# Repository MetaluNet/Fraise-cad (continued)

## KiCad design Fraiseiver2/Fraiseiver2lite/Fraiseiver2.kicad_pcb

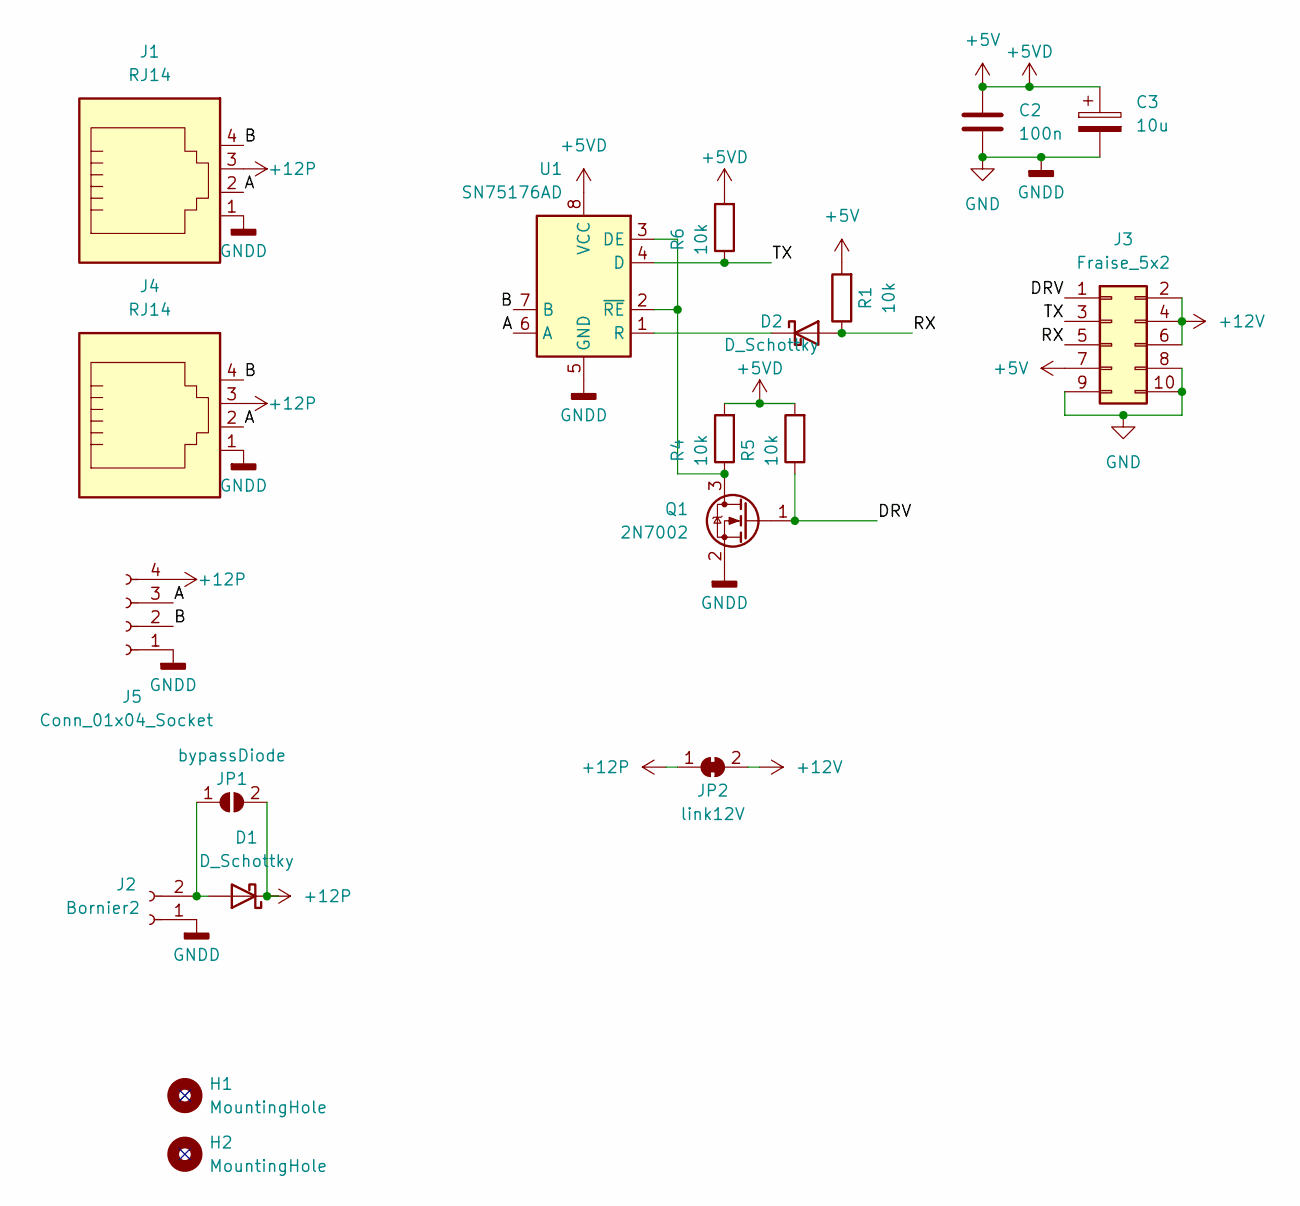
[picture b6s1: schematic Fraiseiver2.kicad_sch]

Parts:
C2: 100n; C_Rect_L4.6mm_W2.0mm_P2.50mm_MKS02_FKP02
C3: 10u; CP_Radial_D5.0mm_P2.50mm
D1, D2: D_Schottky; D_SMA
H1, H2: MountingHole; MountingHole_3.2mm_M3_Pad_TopOnly
J1, J4: RJ14; RJ11
J2: Bornier2; TerminalBlock_Phoenix_MKDS-3-2-5.08_1x02_P5.08mm_Horizontal
J3: Fraise_5x2; IDC-Header_2x05_P2.54mm_Vertical
J5: Conn_01x04_Socket; TerminalBlock_bornier-4_P5.08mm
JP1: bypassDiode; SolderJumper-2_P1.3mm_Open_RoundedPad1.0x1.5mm
JP2: link12V; SolderJumper-2_P1.3mm_Bridged_RoundedPad1.0x1.5mm
Q1: 2N7002; SOT-23
R1, R4, R5, R6: 10k; R_Axial_DIN0204_L3.6mm_D1.6mm_P5.08mm_Horizontal
U1: SN75176AD; SOIC-8_3.9x4.9mm_P1.27mm

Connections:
+5V: C2.1, C3.1, J3.7, R1.2, R4.2, R5.2, R6.2, U1.8 (VCC)
+12P: D1.1 (K), J1.3, J4.3, J5.4, JP1.2 (B), JP2.1 (A)
+12V: J3.2, J3.4, J3.6, JP2.2 (B)
/A: J1.2, J4.2, J5.3, U1.6 (A)
/B: J1.4, J4.4, J5.2, U1.7 (B)
/DRV: J3.1, Q1.1 (G), R5.1
/RX: D2.2 (A), J3.5, R1.1
/TX: J3.3, R6.1, U1.4 (D)
GND: C2.2, C3.2, J1.1, J2.1, J3.8, J3.9, J3.10, J4.1, J5.1, Q1.2 (S), U1.5 (GND)
unnamed: D1.2 (A), J2.2, JP1.1 (A)
unnamed: D2.1 (K), U1.1 (R)
unnamed: Q1.3 (D), R4.1, U1.2 (~RE), U1.3 (DE)

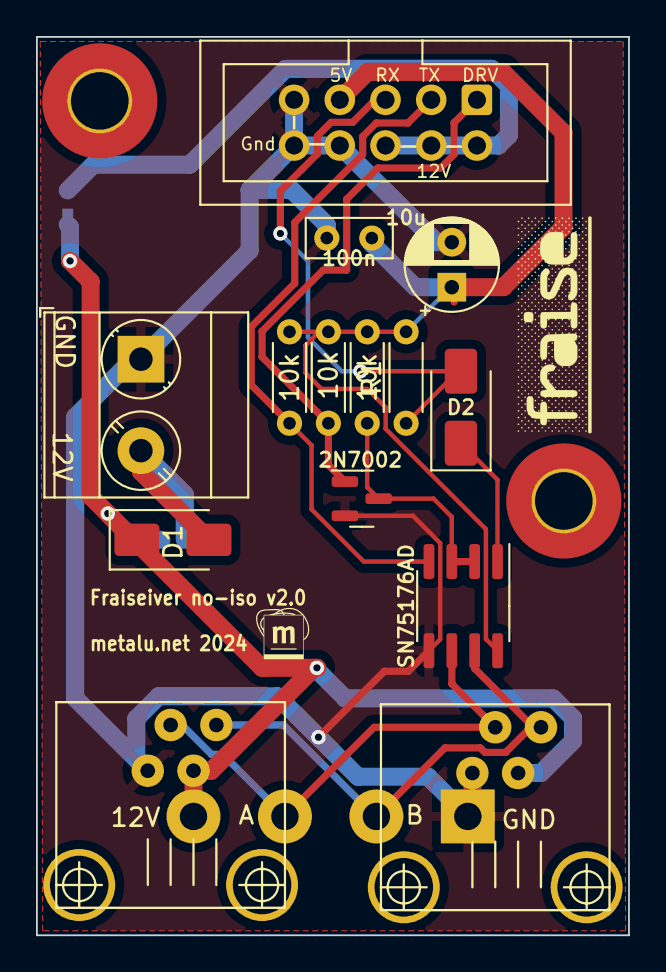
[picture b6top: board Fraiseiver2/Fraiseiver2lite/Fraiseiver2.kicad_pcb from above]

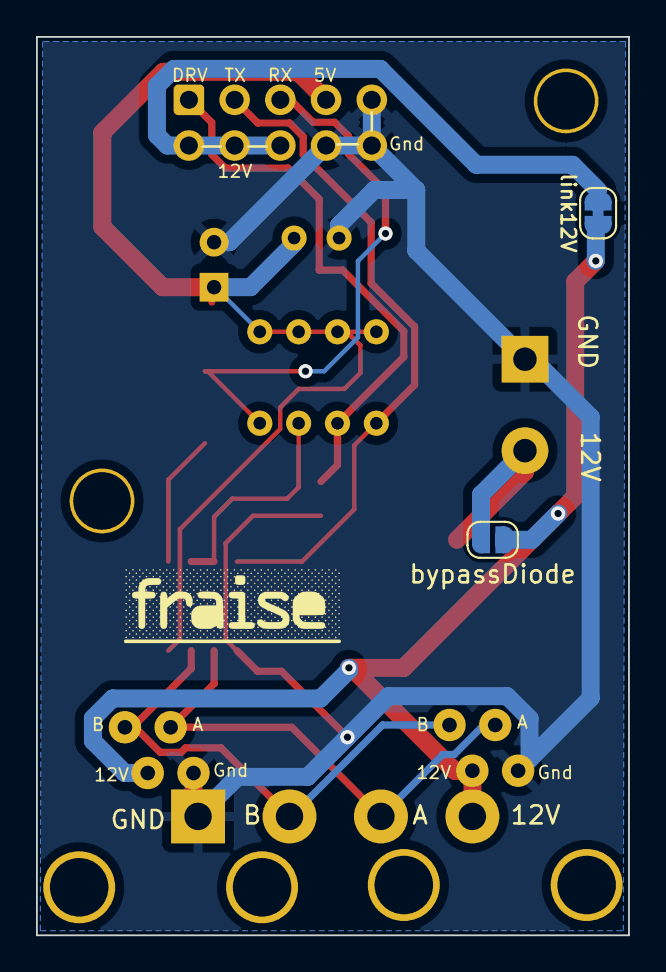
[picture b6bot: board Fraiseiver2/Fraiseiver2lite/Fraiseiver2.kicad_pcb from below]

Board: 2 copper layers, 32.9 x 49.9 mm, 19 parts (2 on the bottom side), 12 nets.

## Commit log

2024-10-01 add Fraiseiver2, Fraiseiver2lite, PicoFraise, PicoFraiseJST
2024-11-26 new Fraiseiver3, based on ADM2484-like (or ADM2463)
2024-11-26 new PicoMot board, based on VNH7070
2024-11-26 new Clamp1 board for protecting pico inputs
2024-11-26 update PicoFraiseJST
2024-11-26 add gerber/ in .gitignore
